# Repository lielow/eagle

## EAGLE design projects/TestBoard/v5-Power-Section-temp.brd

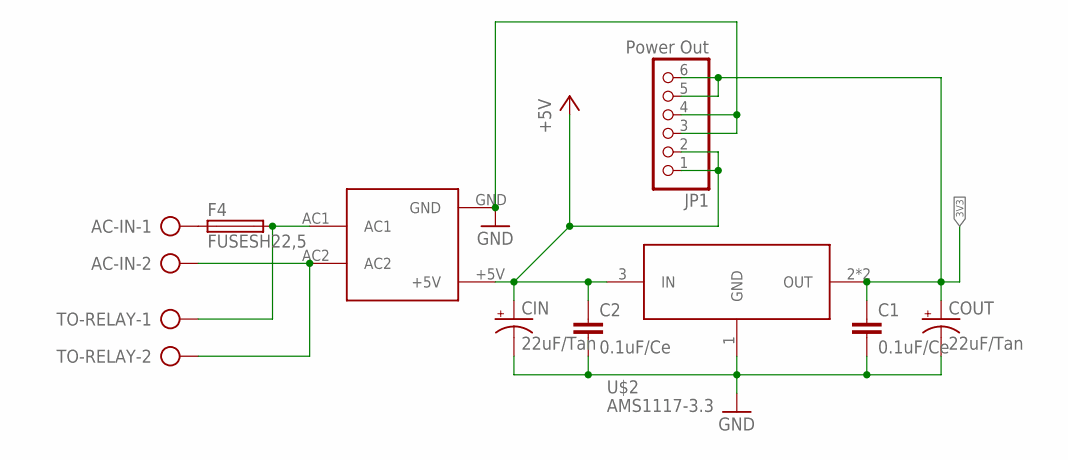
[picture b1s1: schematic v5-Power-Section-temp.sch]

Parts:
AC-IN: AK300/2
C1, C2: 0.1uF/Ce; C025-024X044
CIN: 22uF/Tan; E2,5-5
COUT: 22uF/Tan; E2,5-5
F4: FUSESH22,5; SH22,5
JP1: Power Out; 1X06
TO-RELAY: AK300/2
U$1: HLK-PM01
U$2: AMS1117-3.3; SOT-223

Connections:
3V3: C1.1, COUT.+, JP1.5, JP1.6, U$2.2 (OUT), U$2.4 (OUT)
+5V: C2.1, CIN.+, JP1.1, JP1.2, U$1.+5V, U$2.3 (IN)
GND: C1.2, C2.2, CIN.-, COUT.-, JP1.3, JP1.4, U$1.GND, U$2.1 (GND)
unnamed: AC-IN.1, F4.1
unnamed: AC-IN.2, TO-RELAY.2, U$1.AC2
RELAY-NO: F4.2, TO-RELAY.1, U$1.AC1

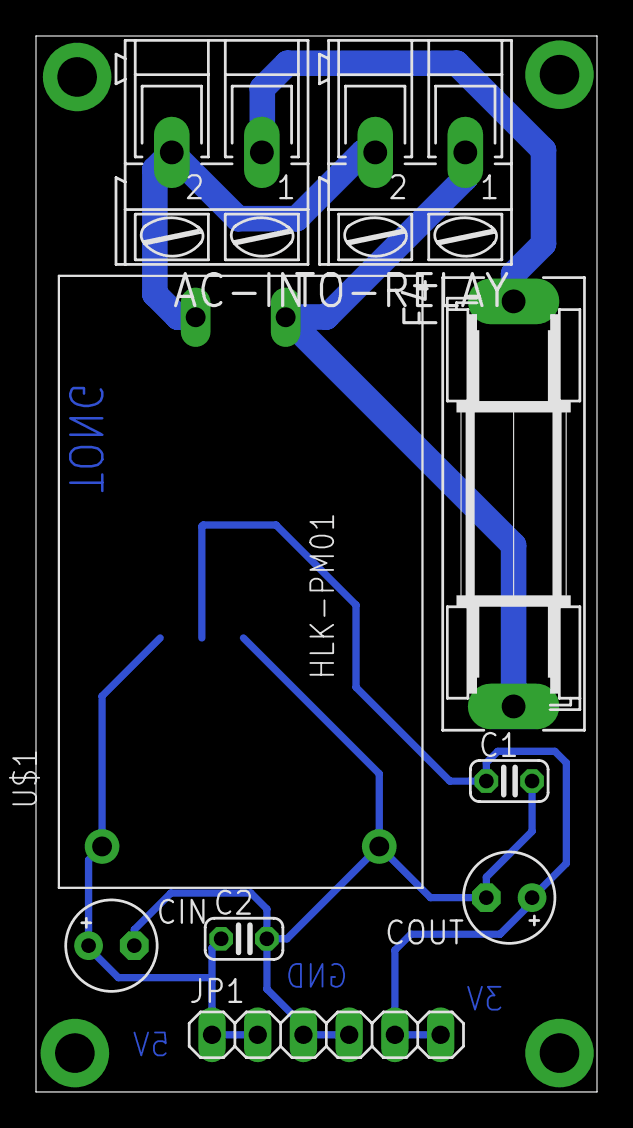
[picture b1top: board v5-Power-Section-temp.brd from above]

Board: 2 copper layers, 31.2 x 58.7 mm, 10 parts (1 on the bottom side), 6 nets.

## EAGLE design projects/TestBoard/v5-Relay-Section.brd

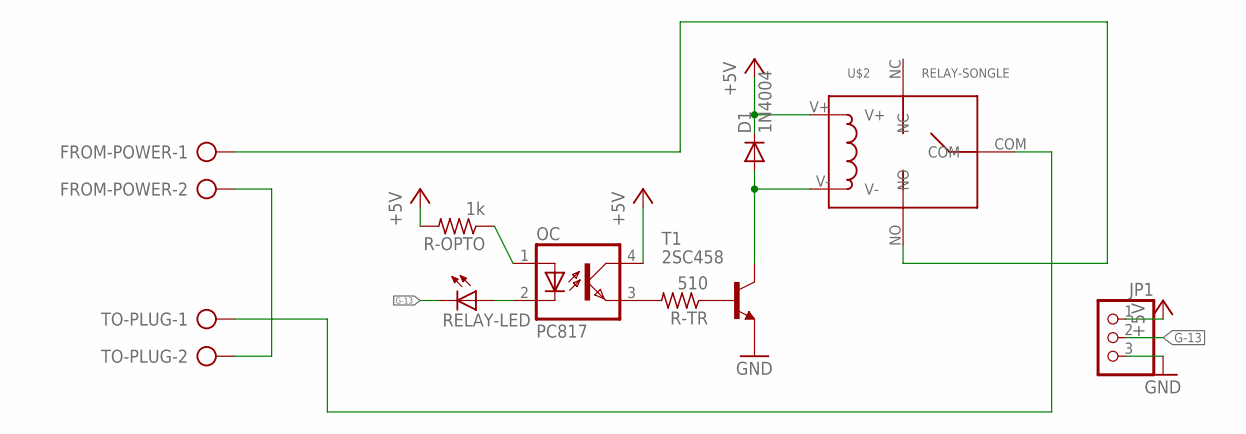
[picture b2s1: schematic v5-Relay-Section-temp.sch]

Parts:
D1: 1N4004; DO41-10
FROM-POWER: AK300/2
JP1: PINHD-1X3; 1X03
OC: PC817; DIL04
R-OPTO: 1k; 0207/7
R-TR: 510; 0207/7
RELAY-LED: LED3MM
T1: 2SC458; TO92-ECB
TO-PLUG: AK300/2
U$2: RELAY-SONGLE

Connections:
+5V: D1.C, JP1.1, OC.4 (COL), R-OPTO.2, U$2.V+
G-13: JP1.2, RELAY-LED.K (C)
GND: JP1.3, T1.E
unnamed: OC.3 (EMIT), R-TR.2
unnamed: R-TR.1, T1.B
unnamed: FROM-POWER.2, TO-PLUG.2
unnamed: FROM-POWER.1, U$2.NO
unnamed: TO-PLUG.1, U$2.COM
unnamed: OC.2 (C), RELAY-LED.A
unnamed: OC.1 (A), R-OPTO.1
unnamed: D1.A, T1.C, U$2.V-

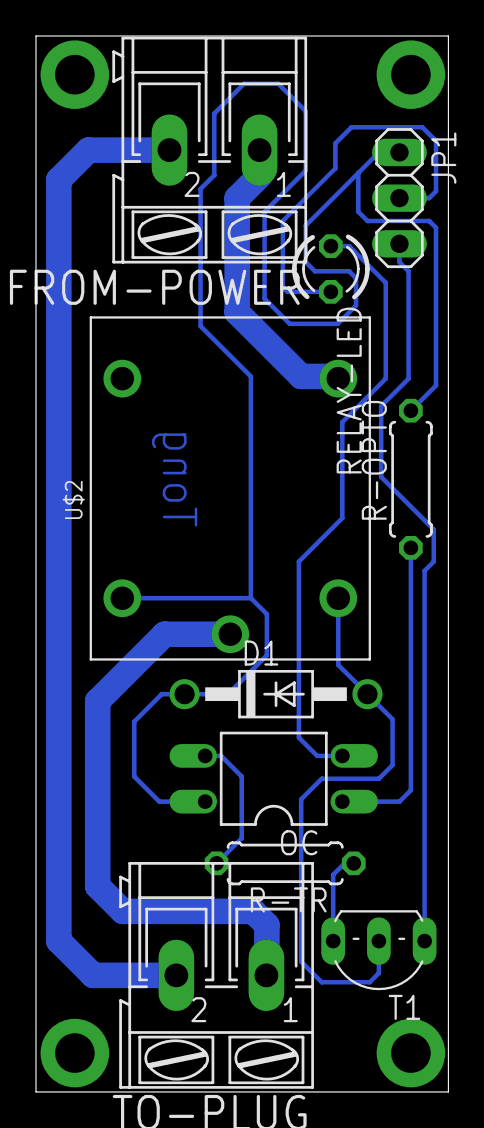
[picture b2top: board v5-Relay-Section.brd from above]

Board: 2 copper layers, 22.9 x 58.7 mm, 10 parts (0 on the bottom side), 11 nets.

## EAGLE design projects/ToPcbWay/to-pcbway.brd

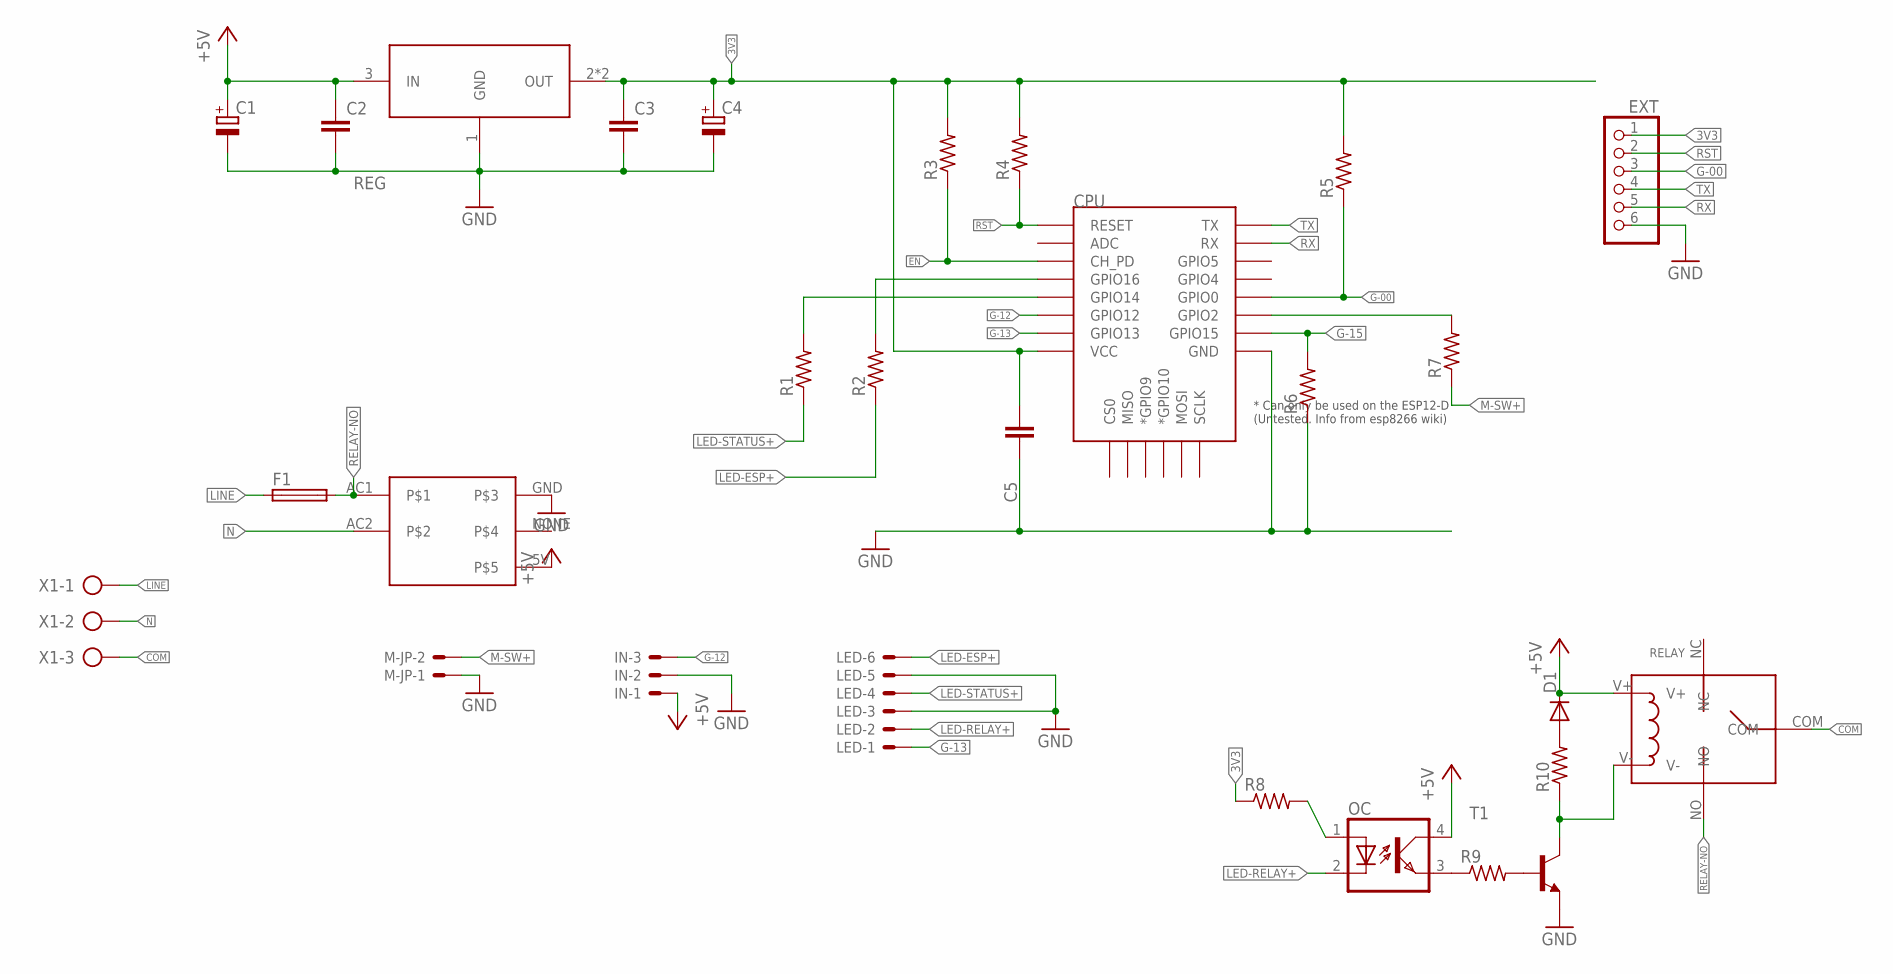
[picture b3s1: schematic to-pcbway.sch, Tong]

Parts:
C1, C4: CPOL-EUE2-5; E2-5
C2, C3: C-EUC0603K; C0603K
C5: C-EUC0805; C0805
CPU: ESP12ESMD; ESP12E-SMD
D1: 1N4148DO35-7; DO35-7
EXT: PINHD-1X6; 1X06
F1: FUSESH22,5; SH22,5
IN: 53048-03
LED: 53048-06
M-JP: 53048-02
OC: PC817; DIL04
R1, R2, R3, R4, R5, R6, R7: R-US_R0603; R0603
R8, R9, R10: R-US_M0805; M0805
REG: AMS1117-3.3; SOT-223
RELAY: RELAY-SONGLE
T1: BC817-NPN-SOT23-BEC; SOT23-BEC
U$4: POWERSUPPLY-5V-700MA
X1: AK300/3

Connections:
3V3: C3.1, C4.+, C5.1, CPU.VCC, EXT.1, R3.2, R4.2, R5.2, R8.1, REG.2 (OUT), REG.4 (OUT)
+5V: C1.+, C2.1, D1.C, IN.1, OC.4 (COL), REG.3 (IN), RELAY.V+, U$4.5V
COM: RELAY.COM, X1.3
EN: CPU.CH_PD, R3.1
G-00: CPU.GPIO0, EXT.3, R5.1
G-12: CPU.GPIO12, IN.3
G-13: CPU.GPIO13, LED.1
G-15: CPU.GPIO15, R6.2
GND: C1.-, C2.2, C3.2, C4.-, C5.2, CPU.GND, EXT.6, IN.2, LED.3, LED.5, M-JP.1, R6.1, REG.1 (GND), T1.E, U$4.GND
LED-ESP+: LED.6, R2.1
LED-RELAY+: LED.2, OC.2 (C)
LED-STATUS+: LED.4, R1.1
LINE: F1.1, X1.1
M-SW+: M-JP.2, R7.1
N: U$4.AC2, X1.2
unnamed: OC.3 (EMIT), R9.1
unnamed: R9.2, T1.B
unnamed: CPU.GPIO16, R2.2
unnamed: CPU.GPIO2, R7.2
unnamed: CPU.GPIO14, R1.2
unnamed: OC.1 (A), R8.2
unnamed: D1.A, R10.2
unnamed: R10.1, RELAY.V-, T1.C
RELAY-NO: F1.2, RELAY.NO, U$4.AC1
RST: CPU.RESET, EXT.2, R4.1
RX: CPU.RXD0 (RX), EXT.5
TX: CPU.TXD0 (TX), EXT.4

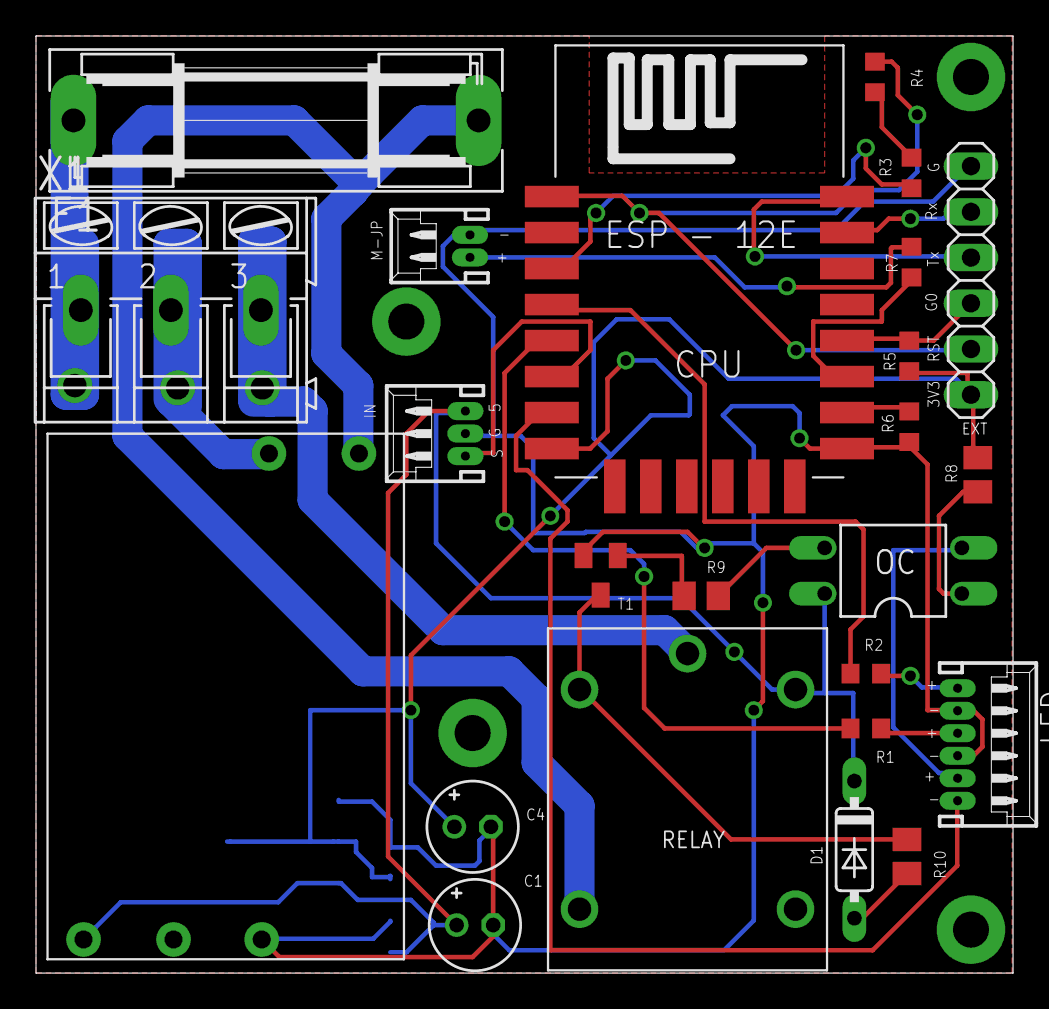
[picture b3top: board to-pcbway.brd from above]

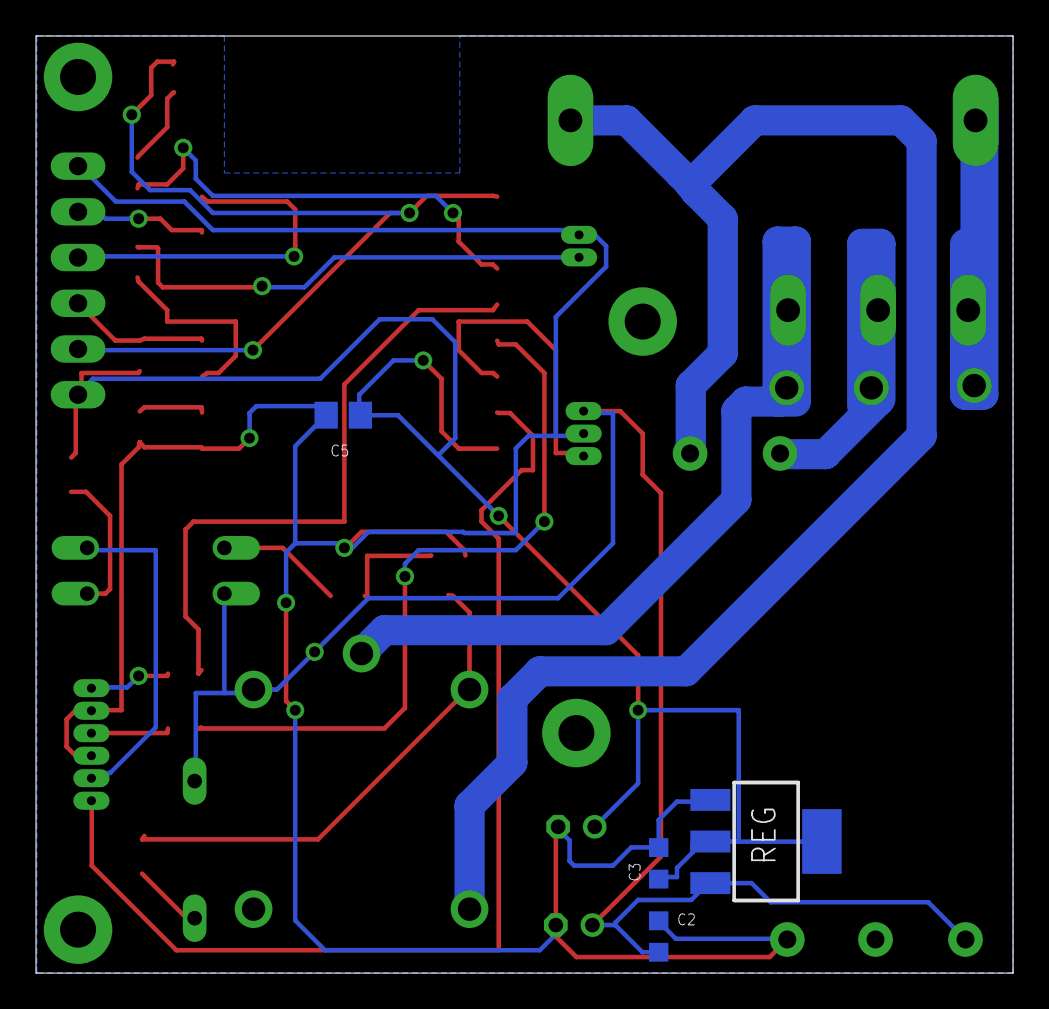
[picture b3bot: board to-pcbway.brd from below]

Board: 2 copper layers, 54.3 x 52.1 mm, 28 parts (4 on the bottom side), 27 nets.

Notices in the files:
parts and their libraries:
SparkFun-Aesthetics: Licensing: Creative Commons ShareAlike 4.0 International - https://creativecommons.org/licenses/by-sa/4.0
